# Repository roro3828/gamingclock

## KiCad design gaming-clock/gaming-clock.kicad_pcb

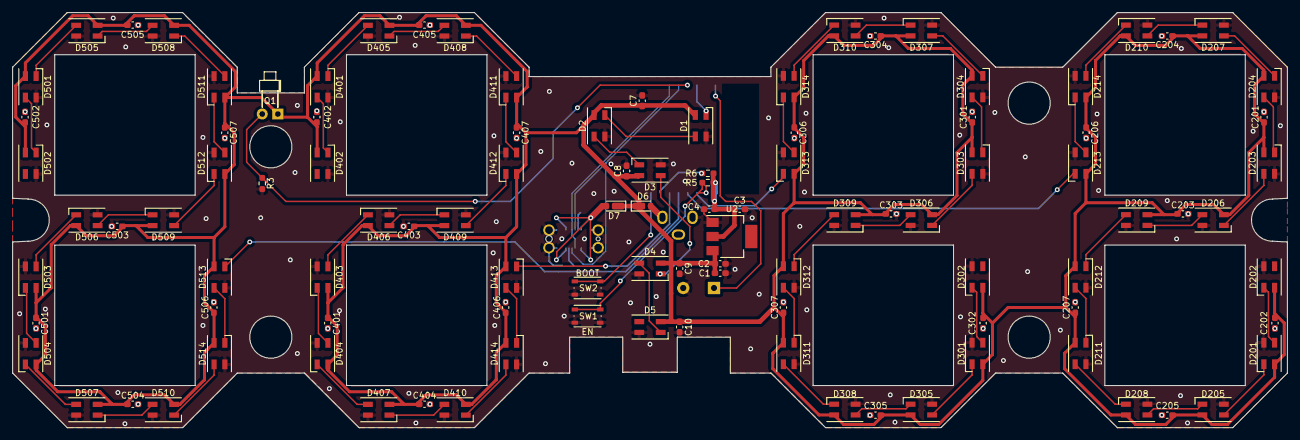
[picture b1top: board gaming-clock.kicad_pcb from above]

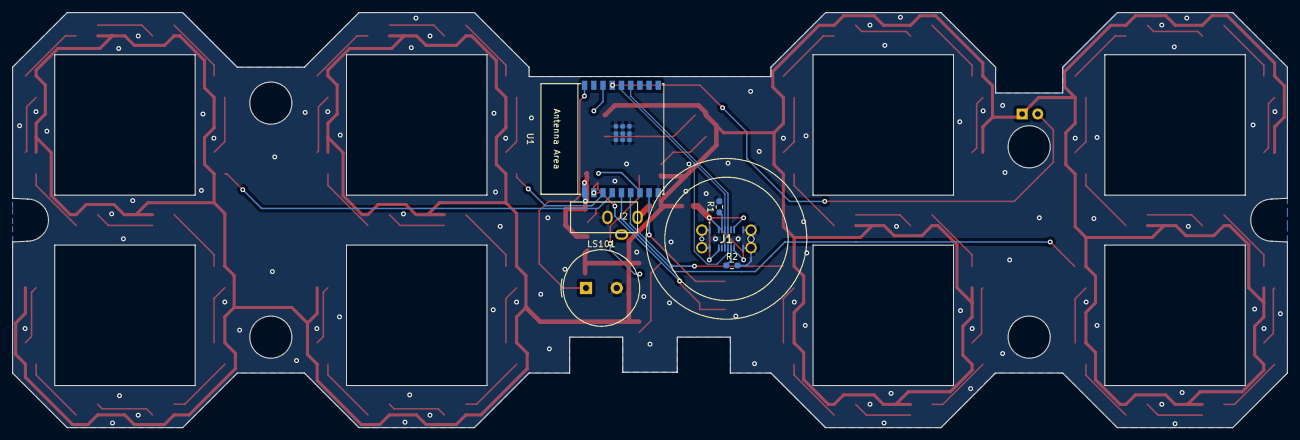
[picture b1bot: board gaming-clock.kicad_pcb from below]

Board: 2 copper layers, 207.5 x 67.6 mm, 112 parts (6 on the bottom side), 75 nets.

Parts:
C1, C4, C7, C8, C9, C10, C201, C202, C203, C204, C205, C206, C207, C301, C302, C303, C304, C305, C306, C307, C401, C402, C403, C404, C405, C406, C407, C501, C502, C503, C504, C505, C506, C507: 10u; C_0603_1608Metric_Pad1.08x0.95mm_HandSolder
C2, C3: 100n; C_0603_1608Metric_Pad1.08x0.95mm_HandSolder
D1, D2, D3, D4, D5, D201, D202, D203, D204, D205, D206, D207, D208, D209, D210, D211, D212, D213, D214, D301, D302, D303, D304, D305, D306, D307, D308, D309, D310, D311, D312, D313, D314, D401, D402, D403, D404, D405, D406, D407, D408, D409, D410, D411, D412, D413, D414, D501, D502, D503, D504, D505, D506, D507, D508, D509, D510, D511, D512, D513, D514: SK6812MINI; LED_SK6812MINI_PLCC4_3.5x3.5mm_P1.75mm
D6, D7: D_Schottky; D_TUMD2
J1: USB4145-03-0230-C; USB4145030230C
J2: Barrel_Jack_Switch; 1.3mmDCjack
LS101: Speaker; Buzzer_TDK_PS1240P02BT_D12.2mm_H6.5mm
Q1: Q_Photo_NPN_CE; LED_D1.8mm_W1.8mm_H2.4mm_Horizontal_O3.81mm_Z1.6mm
R1, R2: 5.1k; R_0603_1608Metric_Pad0.98x0.95mm_HandSolder
R3: 100k; R_0603_1608Metric_Pad0.98x0.95mm_HandSolder
R5, R6: 10k; R_0603_1608Metric_Pad0.98x0.95mm_HandSolder
SW1: EN; SW_Push_1P1T_NO_Vertical_Wuerth_434133025816
SW2: BOOT; SW_Push_1P1T_NO_Vertical_Wuerth_434133025816
U1: ESP32-C3-WROOM-02
U2: LM1117GS-3.3; SOT-223

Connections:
+3.3V: C3.1, C4.1, R5.1, R6.1, U1.1 (3V3), U2.2 (VO)
+5V: C1.1, C2.1, C7.1, C8.1, C9.1, C10.1, C201.1, C202.1, C203.1, C204.1, C205.1, C206.1, C207.1, C301.1, C302.1, C303.1, C304.1, C305.1, C306.1, C307.1, C401.1, C402.1, C403.1, C404.1, C405.1, C406.1, C407.1, C501.1, C502.1, C503.1, C504.1, C505.1, C506.1, C507.1, D1.4 (VDD), D2.4 (VDD), D3.4 (VDD), D4.4 (VDD), D5.4 (VDD), D6.1 (K), D7.1 (K), D201.4 (VDD), D202.4 (VDD), D203.4 (VDD), D204.4 (VDD), D205.4 (VDD), D206.4 (VDD), D207.4 (VDD), D208.4 (VDD), D209.4 (VDD), D210.4 (VDD), D211.4 (VDD), D212.4 (VDD), D213.4 (VDD), D214.4 (VDD), D301.4 (VDD), D302.4 (VDD), D303.4 (VDD), D304.4 (VDD), D305.4 (VDD), D306.4 (VDD), D307.4 (VDD), D308.4 (VDD), D309.4 (VDD), D310.4 (VDD), D311.4 (VDD), D312.4 (VDD), D313.4 (VDD), D314.4 (VDD), D401.4 (VDD), D402.4 (VDD), D403.4 (VDD), D404.4 (VDD), D405.4 (VDD), D406.4 (VDD), D407.4 (VDD), D408.4 (VDD), D409.4 (VDD), D410.4 (VDD), D411.4 (VDD), D412.4 (VDD), D413.4 (VDD), D414.4 (VDD), D501.4 (VDD), D502.4 (VDD), D503.4 (VDD), D504.4 (VDD), D505.4 (VDD), D506.4 (VDD), D507.4 (VDD), D508.4 (VDD), D509.4 (VDD), D510.4 (VDD), D511.4 (VDD), D512.4 (VDD), D513.4 (VDD), D514.4 (VDD), Q1.1 (C), U2.3 (VI)
/Sheetname: 7-Segment-ARGB1/DIN: D313.3 (DIN), U1.3 (GPIO4/ADC1_CH4)
/Sheetname: 7-Segment-ARGB2/DIN: D213.3 (DIN), U1.4 (GPIO5/ADC2_CH0)
/Sheetname: 7-Segment-ARGB3/DIN: D413.3 (DIN), U1.6 (GPIO7)
/Sheetname: 7-Segment-ARGB4/DIN: D513.3 (DIN), U1.5 (GPIO6)
D+: J1.A6 (DP1), J1.B6 (DP2), U1.14 (GPIO19/USB_D+)
D-: J1.A7 (DN1), J1.B7 (DN2), U1.13 (GPIO18/USB_D-)
DC5V: D6.2 (A), J2.1
GND: C1.2, C2.2, C3.2, C4.2, C7.2, C8.2, C9.2, C10.2, C201.2, C202.2, C203.2, C204.2, C205.2, C206.2, C207.2, C301.2, C302.2, C303.2, C304.2, C305.2, C306.2, C307.2, C401.2, C402.2, C403.2, C404.2, C405.2, C406.2, C407.2, C501.2, C502.2, C503.2, C504.2, C505.2, C506.2, C507.2, D1.2 (VSS), D2.2 (VSS), D3.2 (VSS), D4.2 (VSS), D5.2 (VSS), D201.2 (VSS), D202.2 (VSS), D203.2 (VSS), D204.2 (VSS), D205.2 (VSS), D206.2 (VSS), D207.2 (VSS), D208.2 (VSS), D209.2 (VSS), D210.2 (VSS), D211.2 (VSS), D212.2 (VSS), D213.2 (VSS), D214.2 (VSS), D301.2 (VSS), D302.2 (VSS), D303.2 (VSS), D304.2 (VSS), D305.2 (VSS), D306.2 (VSS), D307.2 (VSS), D308.2 (VSS), D309.2 (VSS), D310.2 (VSS), D311.2 (VSS), D312.2 (VSS), D313.2 (VSS), D314.2 (VSS), D401.2 (VSS), D402.2 (VSS), D403.2 (VSS), D404.2 (VSS), D405.2 (VSS), D406.2 (VSS), D407.2 (VSS), D408.2 (VSS), D409.2 (VSS), D410.2 (VSS), D411.2 (VSS), D412.2 (VSS), D413.2 (VSS), D414.2 (VSS), D501.2 (VSS), D502.2 (VSS), D503.2 (VSS), D504.2 (VSS), D505.2 (VSS), D506.2 (VSS), D507.2 (VSS), D508.2 (VSS), D509.2 (VSS), D510.2 (VSS), D511.2 (VSS), D512.2 (VSS), D513.2 (VSS), D514.2 (VSS), J1.A1 (GND_1), J1.A12 (GND_2), J1.B1 (GND_3), J1.B12 (GND_4), J1.MH1 (MH5), J1.MH2 (MH6), J1.MH3, J1.MH4, J2.2, LS101.2, R1.2, R2.2, R3.2, SW1.2, SW2.2, U1.9 (GND), U1.19 (GND), U2.1 (GND)
GPIO8: R6.2, U1.7 (GPIO8)
GPIO9: SW2.1, U1.8 (GPIO9)
LS: Q1.2 (E), R3.1, U1.15 (GPIO3/ADC1_CH3)
unnamed: D1.1 (DOUT), D2.3 (DIN)
unnamed: D2.1 (DOUT), D3.3 (DIN)
unnamed: D3.1 (DOUT), D4.3 (DIN)
unnamed: D4.1 (DOUT), D5.3 (DIN)
unnamed: D201.3 (DIN), D205.1 (DOUT)
unnamed: D201.1 (DOUT), D202.3 (DIN)
unnamed: D203.3 (DIN), D204.1 (DOUT)
unnamed: D203.1 (DOUT), D206.3 (DIN)
unnamed: D204.3 (DIN), D207.1 (DOUT)
unnamed: D205.3 (DIN), D208.1 (DOUT)
unnamed: D206.1 (DOUT), D209.3 (DIN)
unnamed: D207.3 (DIN), D210.1 (DOUT)
unnamed: D208.3 (DIN), D211.1 (DOUT)
unnamed: D209.1 (DOUT), D212.3 (DIN)
unnamed: D210.3 (DIN), D214.1 (DOUT)
unnamed: D211.3 (DIN), D212.1 (DOUT)
unnamed: D213.1 (DOUT), D214.3 (DIN)
unnamed: D301.3 (DIN), D305.1 (DOUT)
unnamed: D301.1 (DOUT), D302.3 (DIN)
unnamed: D303.3 (DIN), D304.1 (DOUT)
unnamed: D303.1 (DOUT), D306.3 (DIN)
unnamed: D304.3 (DIN), D307.1 (DOUT)
unnamed: D305.3 (DIN), D308.1 (DOUT)
unnamed: D306.1 (DOUT), D309.3 (DIN)
unnamed: D307.3 (DIN), D310.1 (DOUT)
unnamed: D308.3 (DIN), D311.1 (DOUT)
unnamed: D309.1 (DOUT), D312.3 (DIN)
unnamed: D310.3 (DIN), D314.1 (DOUT)
unnamed: D311.3 (DIN), D312.1 (DOUT)
unnamed: D313.1 (DOUT), D314.3 (DIN)
unnamed: D401.3 (DIN), D405.1 (DOUT)
unnamed: D401.1 (DOUT), D402.3 (DIN)
unnamed: D403.3 (DIN), D404.1 (DOUT)
unnamed: D403.1 (DOUT), D406.3 (DIN)
unnamed: D404.3 (DIN), D407.1 (DOUT)
unnamed: D405.3 (DIN), D408.1 (DOUT)
unnamed: D406.1 (DOUT), D409.3 (DIN)
unnamed: D407.3 (DIN), D410.1 (DOUT)
unnamed: D408.3 (DIN), D411.1 (DOUT)
unnamed: D409.1 (DOUT), D412.3 (DIN)
unnamed: D410.3 (DIN), D414.1 (DOUT)
unnamed: D411.3 (DIN), D412.1 (DOUT)
unnamed: D413.1 (DOUT), D414.3 (DIN)
unnamed: D501.3 (DIN), D505.1 (DOUT)
unnamed: D501.1 (DOUT), D502.3 (DIN)
unnamed: D503.3 (DIN), D504.1 (DOUT)
unnamed: D503.1 (DOUT), D506.3 (DIN)
unnamed: D504.3 (DIN), D507.1 (DOUT)
unnamed: D505.3 (DIN), D508.1 (DOUT)
unnamed: D506.1 (DOUT), D509.3 (DIN)
unnamed: D507.3 (DIN), D510.1 (DOUT)
unnamed: D508.3 (DIN), D511.1 (DOUT)
unnamed: D509.1 (DOUT), D512.3 (DIN)
unnamed: D510.3 (DIN), D514.1 (DOUT)
unnamed: D511.3 (DIN), D512.1 (DOUT)
unnamed: D513.1 (DOUT), D514.3 (DIN)
unnamed: J1.A5 (CC1), R1.1
unnamed: J1.B5 (CC2), R2.1
unnamed: R5.2, SW1.1, U1.2 (EN/CHIP_PU)
SIN: D1.3 (DIN), U1.16 (GPIO2/ADC1_CH2)
SPEAK: LS101.1, U1.18 (GPIO0/ADC1_CH0/XTAL_32K_P)
USB5V: D7.2 (A), J1.A4 (VBUS_1), J1.A9 (VBUS_2), J1.B4 (VBUS_3), J1.B9 (VBUS_4)

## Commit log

2023-07-17 first
2023-07-17 license
2023-07-18 newsheet
2023-07-18 add dcjack
